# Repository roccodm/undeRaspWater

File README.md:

# undeRaspWater

Some useful links:
https://blog.retep.org/2014/02/15/connecting-an-arduino-to-a-raspberry-pi-using-i2c/

https://www.futurashop.it/Allegato_PDF_IT/7100-FT1073K.pdf

https://oscarliang.com/raspberry-pi-arduino-connected-i2c/

http://int03.co.uk/blog/2015/01/11/raspberry-pi-gpio-states-at-boot-time/
https://www.raspberrypi.org/documentation/configuration/pin-configuration.md

Per il voltmetro/amperometro:
http://www.adrirobot.it/arduino/voltmetro_amperometro/Arduino_voltmetro-amperometro.htm

Sulla raspberry vanno dissaldate le resistenza R1 e R2 per garantire il funzionamento del bus I2C quando è spenta. Il pullup è sulla scheda RTC, magari prevedere un pullup da 10K di backup

Per il driver dei led: http://electronics-diy.com/electronic_schematic.php?id=1012

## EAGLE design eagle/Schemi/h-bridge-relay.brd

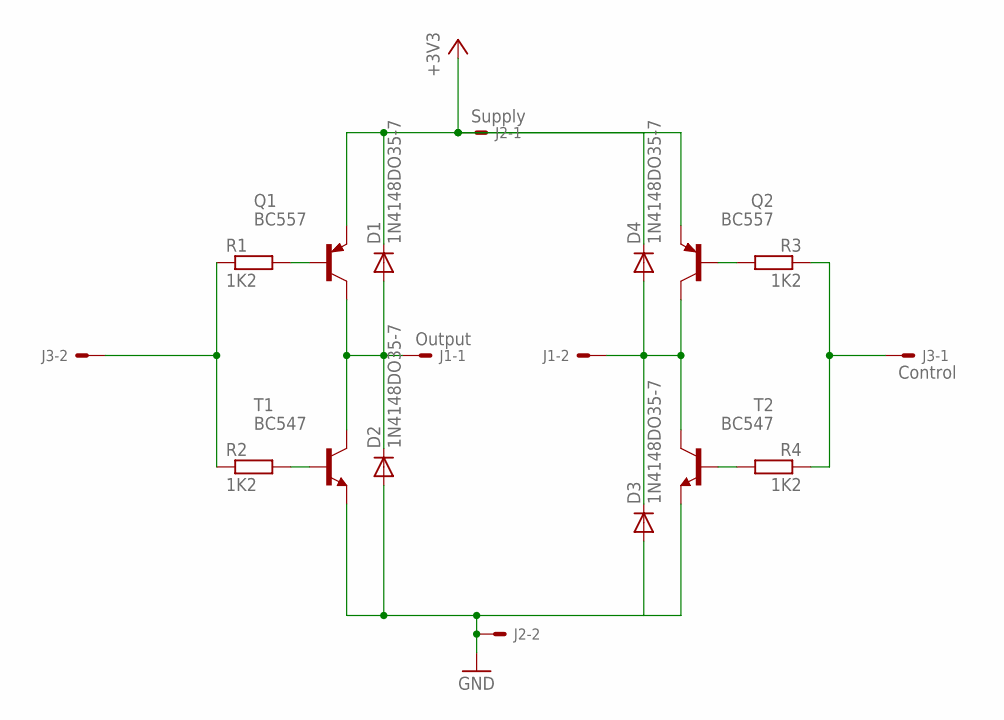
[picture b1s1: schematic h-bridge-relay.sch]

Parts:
D1, D2, D3, D4: 1N4148DO35-7; DO35-7
J1: Output; 6410-02
J2: Supply; 6410-02
J3: Control; 6410-02
Q1, Q2: BC557; TO92
R1, R4: 1K2; 0207/7
R2: 1K2; 0207/12
R3: 1K2; 0207/2V
T1, T2: BC547; TO92

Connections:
+3V3: D1.C, D4.C, J2.1, Q1.1 (E), Q2.1 (E)
GND: D2.A, D3.A, J2.2, T1.1 (E), T2.1 (E)
unnamed: R2.2, T1.2 (B)
unnamed: Q1.2 (B), R1.2
unnamed: Q2.2 (B), R3.2
unnamed: R4.2, T2.2 (B)
unnamed: D1.A, D2.C, J1.1, Q1.3 (C), T1.3 (C)
unnamed: D3.C, D4.A, J1.2, Q2.3 (C), T2.3 (C)
unnamed: J3.1, R3.1, R4.1
unnamed: J3.2, R1.1, R2.1

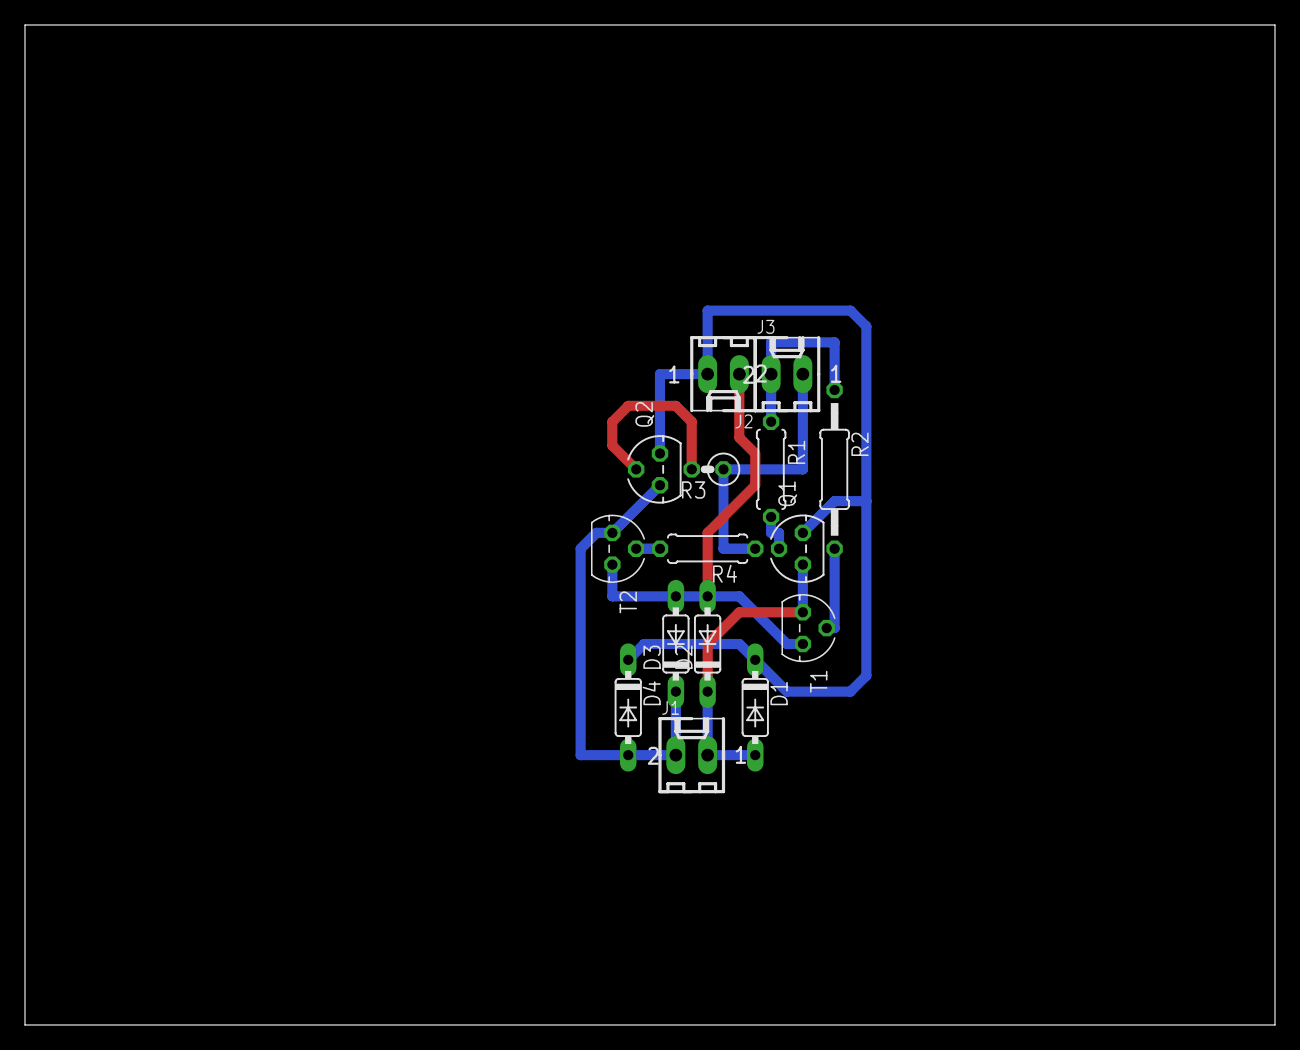
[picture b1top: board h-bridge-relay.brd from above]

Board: 2 copper layers, 100.0 x 80.0 mm, 15 parts (0 on the bottom side), 10 nets.

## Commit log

2017-01-22 prima stesura con materiale preso in giro
2017-01-24 inserito esempio per arduino
2017-02-02 Riorganizzato repository
2017-02-02 Completato script lato raspberry
2017-02-02 Aggiunti primi schemi
2017-02-02 Migliorato firmware arduino, spostate routine accensione raspberry in apposita funzione, risolti problemi su wt
2017-02-02 fixed some bug
2017-02-03 added 74hc466 on board and added code to manage on arduino
2017-02-03 added hardware feedback from raspberry. Solved some issue
2017-02-03 rewritten voltage read function
2017-02-06 added get_pin_median(). Rewritten set_eprom_datetime()
2017-02-06 added watchdog support, rewitten set_rtc_datetime()
2017-02-06 solved little issues, added python source for broadcast messages
2017-02-06 broadcast script first release
2017-02-07 bug risolti su arduino
2017-02-15 eliminato watchdog (commentate righe): arduino pro mini non lo supporta al momento bene
2018-02-01 aggiornato ad ultima versione
2018-02-08 Add raspberry pi scripts
2018-02-08 Initial work on version 2
2018-02-08 Add build file for CLI
2018-02-08 Use single timer (timer1) set to 1hz
2018-02-08 Clang format + move defines to defines.h
2018-02-09 Work on rpi start/stop
2018-02-09 Add gitignore
2018-02-09 Forgot to add defines.h in previous commit
2018-02-09 Move RPI handling functions to rpi.ino
2018-02-09 Move more functions to rpi.ino
2018-02-09 Add serial handling, keep alive option
2018-02-09 Add heartbeat, voltage, amp, watts, temp to user interface
2018-02-09 Add RPI mode, diff rpi_has_power, rpi_is_running
2018-02-09 Aggiunti nuovi script
2018-02-09 Bring back many functions from v1
2018-02-10 Refactori user_interface/atoi/atod
2018-02-10 Refactor print_menu and atod
2018-02-10 Add error message to set rtc
2018-02-10 Sort pin order in define
2018-02-11 Add some options for breadboard debugging
2018-02-11 Add diagram for how Arduino controls RPI
2018-02-11 Small fix to arduino diagram
2018-02-11 Initial work on diagram implementation
2018-02-11 keepalive->manual_mode, option to reset RPI state.
    Start in manual mode when compiled for breadboard debug.
2018-02-11 Fix setting EEPROM/RTC datetime.
    Properly confiigure restart delay in rpi_setup
2018-02-11 Add option to ask RPI shutdown politely.
    Also add option to see cooldown timer
2018-02-11 Only one cooldown for starting/halting/heartbeat
    Rename rpi_was_alive to rpi_booted
2018-02-12 Serial now expects new line as end of message
    Use separate buffers for i2c and serial input/output
2018-02-12 Rename serial change function from 'k' to 'p'
2018-02-12 Small fix to help menu
2018-02-12 Move static strings to program memory
2018-02-12 Use 3 spaces for tabs as requested by @roccodm
2018-02-13 Add voltage checks
2018-02-13 Add internal clock to be used when RTC is not available
2018-02-13 Add function to set checks results from RPI
2018-02-13 new implementation
2018-02-14 Add correctly timed start/stop
    Will skip cycle if RPI is still running or errors happened.
    Convert .ino files to .cpp to get better compiler checks
    Reorganize includes and global vars.
    Support both 8 and 16 mhz cpus
2018-02-15 added set_led_status()
2018-02-15 Use timer 2 for led switching.
    Four states, off, okay, error, warning
2018-02-15 Use time_t (uint32_t) for time functions
2018-02-15 Set warning LED when rpi checks failed
    Use defines for EEPROM locations and LED
2018-02-15 Remove heartbeat reset
2018-02-15 first working release
2018-02-22 Add blinking green led when running checks
    Led turns green when checks successful, turn off after RPI shutdown
2018-02-22 Use a timer to take voltage and current samples
    The get_pin_median function no longer uses delay but rely on samples taken at
    fixed interval.
2018-02-22 Add 1 sec delay on setup to populate samples.
    Avoid getting wrong Voltage values in the first few loops.
2018-02-22 On valid checks only set green LED if first start
    Turn off led otherwise
2018-03-06 Add bit for manual mode in get_rpi_mode
2018-03-06 ui.py (web interface) almost done; Fixed manual mode in underaspdaemon.py
2018-03-08 Always shut down RPI on boot
    Do not print error messages if not in debug mode
2018-03-09 Do not sample volts and current when reading temp
    analogRead in sampling interrupt seems to screw up the temperature readings
2018-03-10 Implement direct ADC usage.
    Avoid using analogRead which adds delay.
    Analog sensors reading is now done round robin between the desired pins
2018-03-10 Make TIMER2 more precise on 16mhz CPUs
    Does not play well with 64 bits prescaler, so we use a 2000 hz frequency
    and we skip one in the interrupt
2018-03-13 Disable DIRECT_ADC by default
2018-03-28 Added images
2018-05-17 Ensure proper flush in broadcast_receiver
2018-05-17 Add network test script
2018-05-17 Add network test readme
